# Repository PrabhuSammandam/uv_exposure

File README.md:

# uv_exposure
Source code the uv exposure box.

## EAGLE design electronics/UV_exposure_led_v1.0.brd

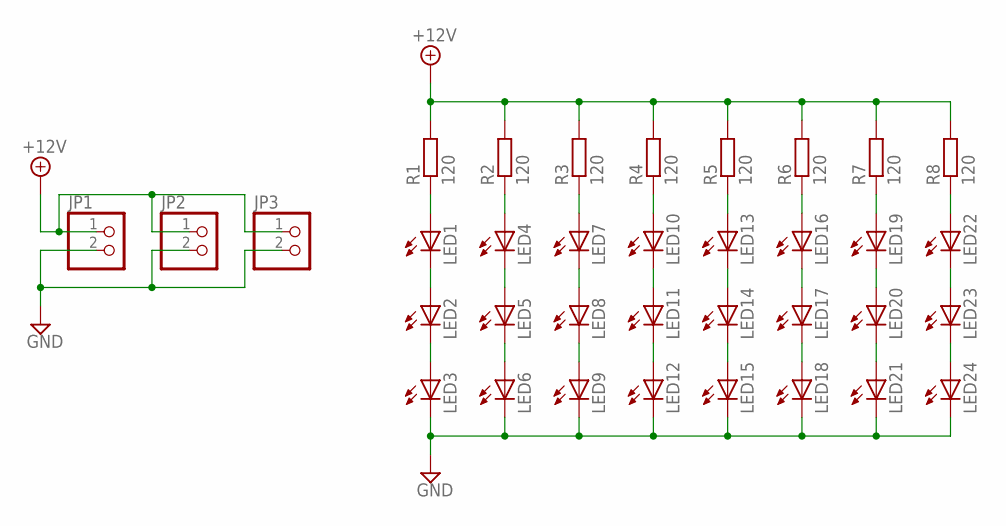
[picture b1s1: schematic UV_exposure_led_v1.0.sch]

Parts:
JP1, JP2, JP3: PINHD-1X2; 1X02
LED1, LED2, LED3, LED4, LED5, LED6, LED7, LED8, LED9, LED10, LED11, LED12, LED13, LED14, LED15, LED16, LED17, LED18, LED19, LED20, LED21, LED22, LED23, LED24: LED5MM
R1, R2, R3, R4, R5, R6, R7, R8: 120; R1206W

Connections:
+12V: JP1.1, JP2.1, JP3.1, R1.2, R2.2, R3.2, R4.2, R5.2, R6.2, R7.2, R8.2
GND: JP1.2, JP2.2, JP3.2, LED3.K (C), LED6.K (C), LED9.K (C), LED12.K (C), LED15.K (C), LED18.K (C), LED21.K (C), LED24.K (C)
unnamed: LED2.K (C), LED3.A
unnamed: LED1.K (C), LED2.A
unnamed: LED1.A, R1.1
unnamed: LED5.K (C), LED6.A
unnamed: LED4.K (C), LED5.A
unnamed: LED4.A, R2.1
unnamed: LED8.K (C), LED9.A
unnamed: LED7.K (C), LED8.A
unnamed: LED7.A, R3.1
unnamed: LED11.K (C), LED12.A
unnamed: LED10.K (C), LED11.A
unnamed: LED10.A, R4.1
unnamed: LED14.K (C), LED15.A
unnamed: LED13.K (C), LED14.A
unnamed: LED13.A, R5.1
unnamed: LED17.K (C), LED18.A
unnamed: LED16.K (C), LED17.A
unnamed: LED16.A, R6.1
unnamed: LED20.K (C), LED21.A
unnamed: LED19.K (C), LED20.A
unnamed: LED19.A, R7.1
unnamed: LED23.K (C), LED24.A
unnamed: LED22.K (C), LED23.A
unnamed: LED22.A, R8.1

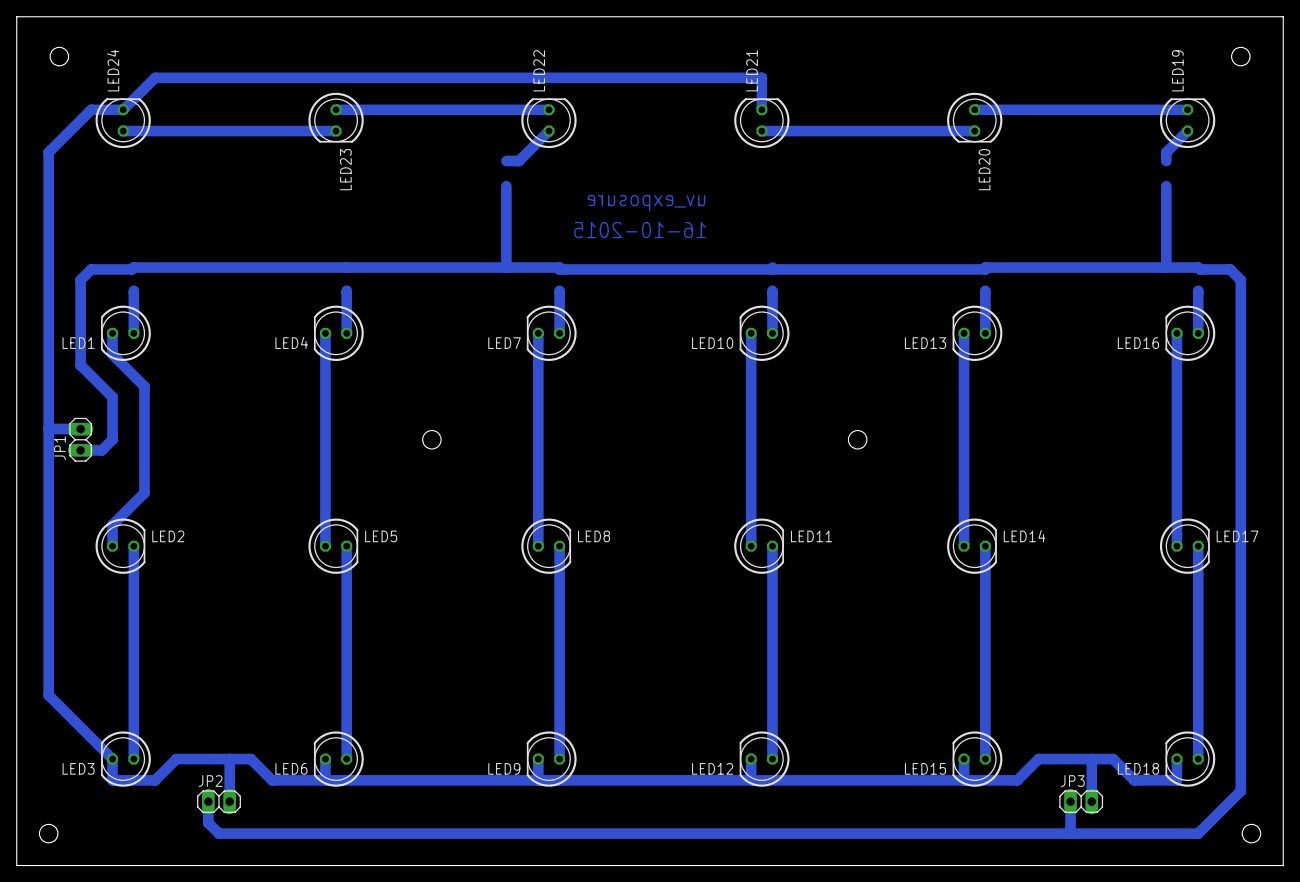
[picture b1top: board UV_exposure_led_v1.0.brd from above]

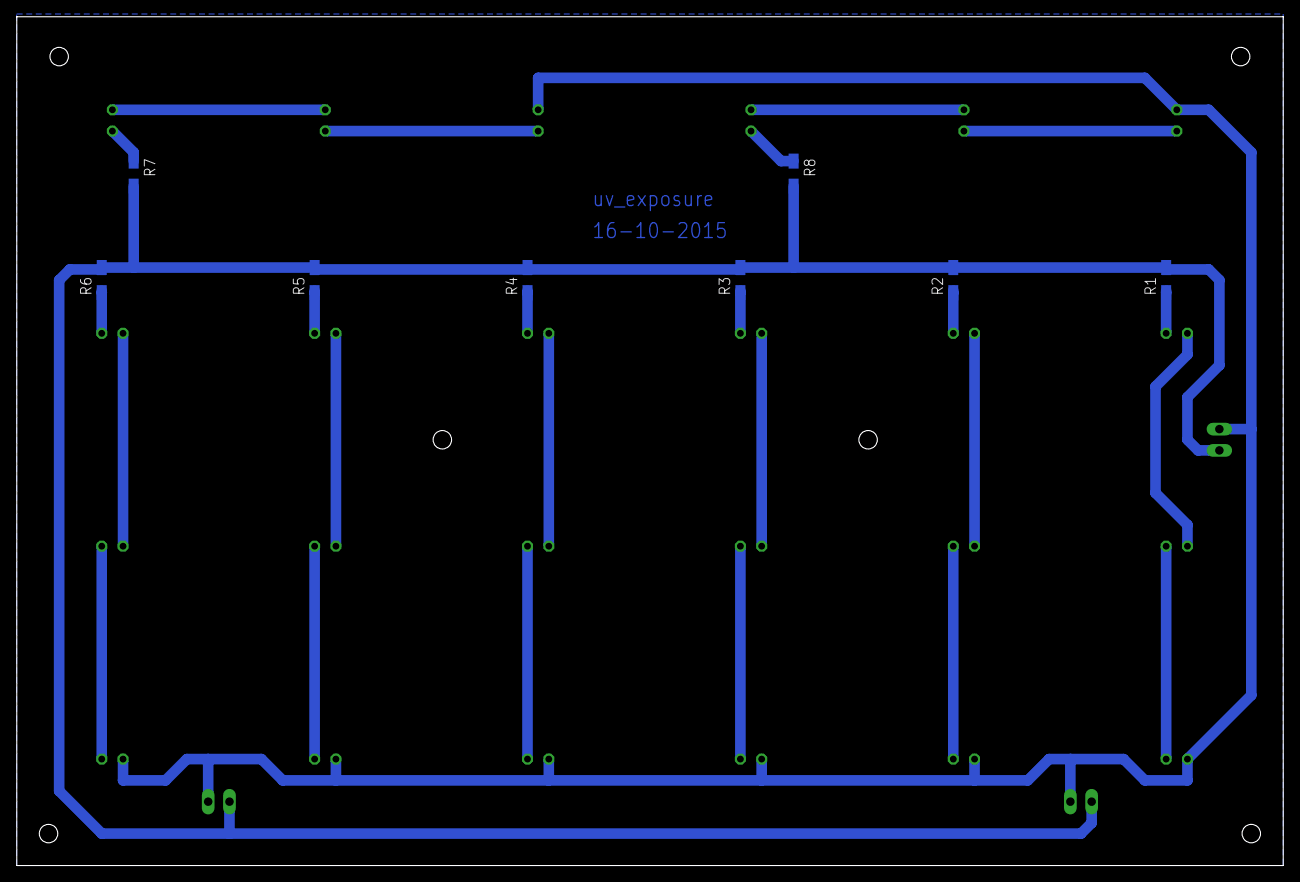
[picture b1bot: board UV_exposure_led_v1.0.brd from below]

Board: 2 copper layers, 151.1 x 101.3 mm, 35 parts (8 on the bottom side), 26 nets.

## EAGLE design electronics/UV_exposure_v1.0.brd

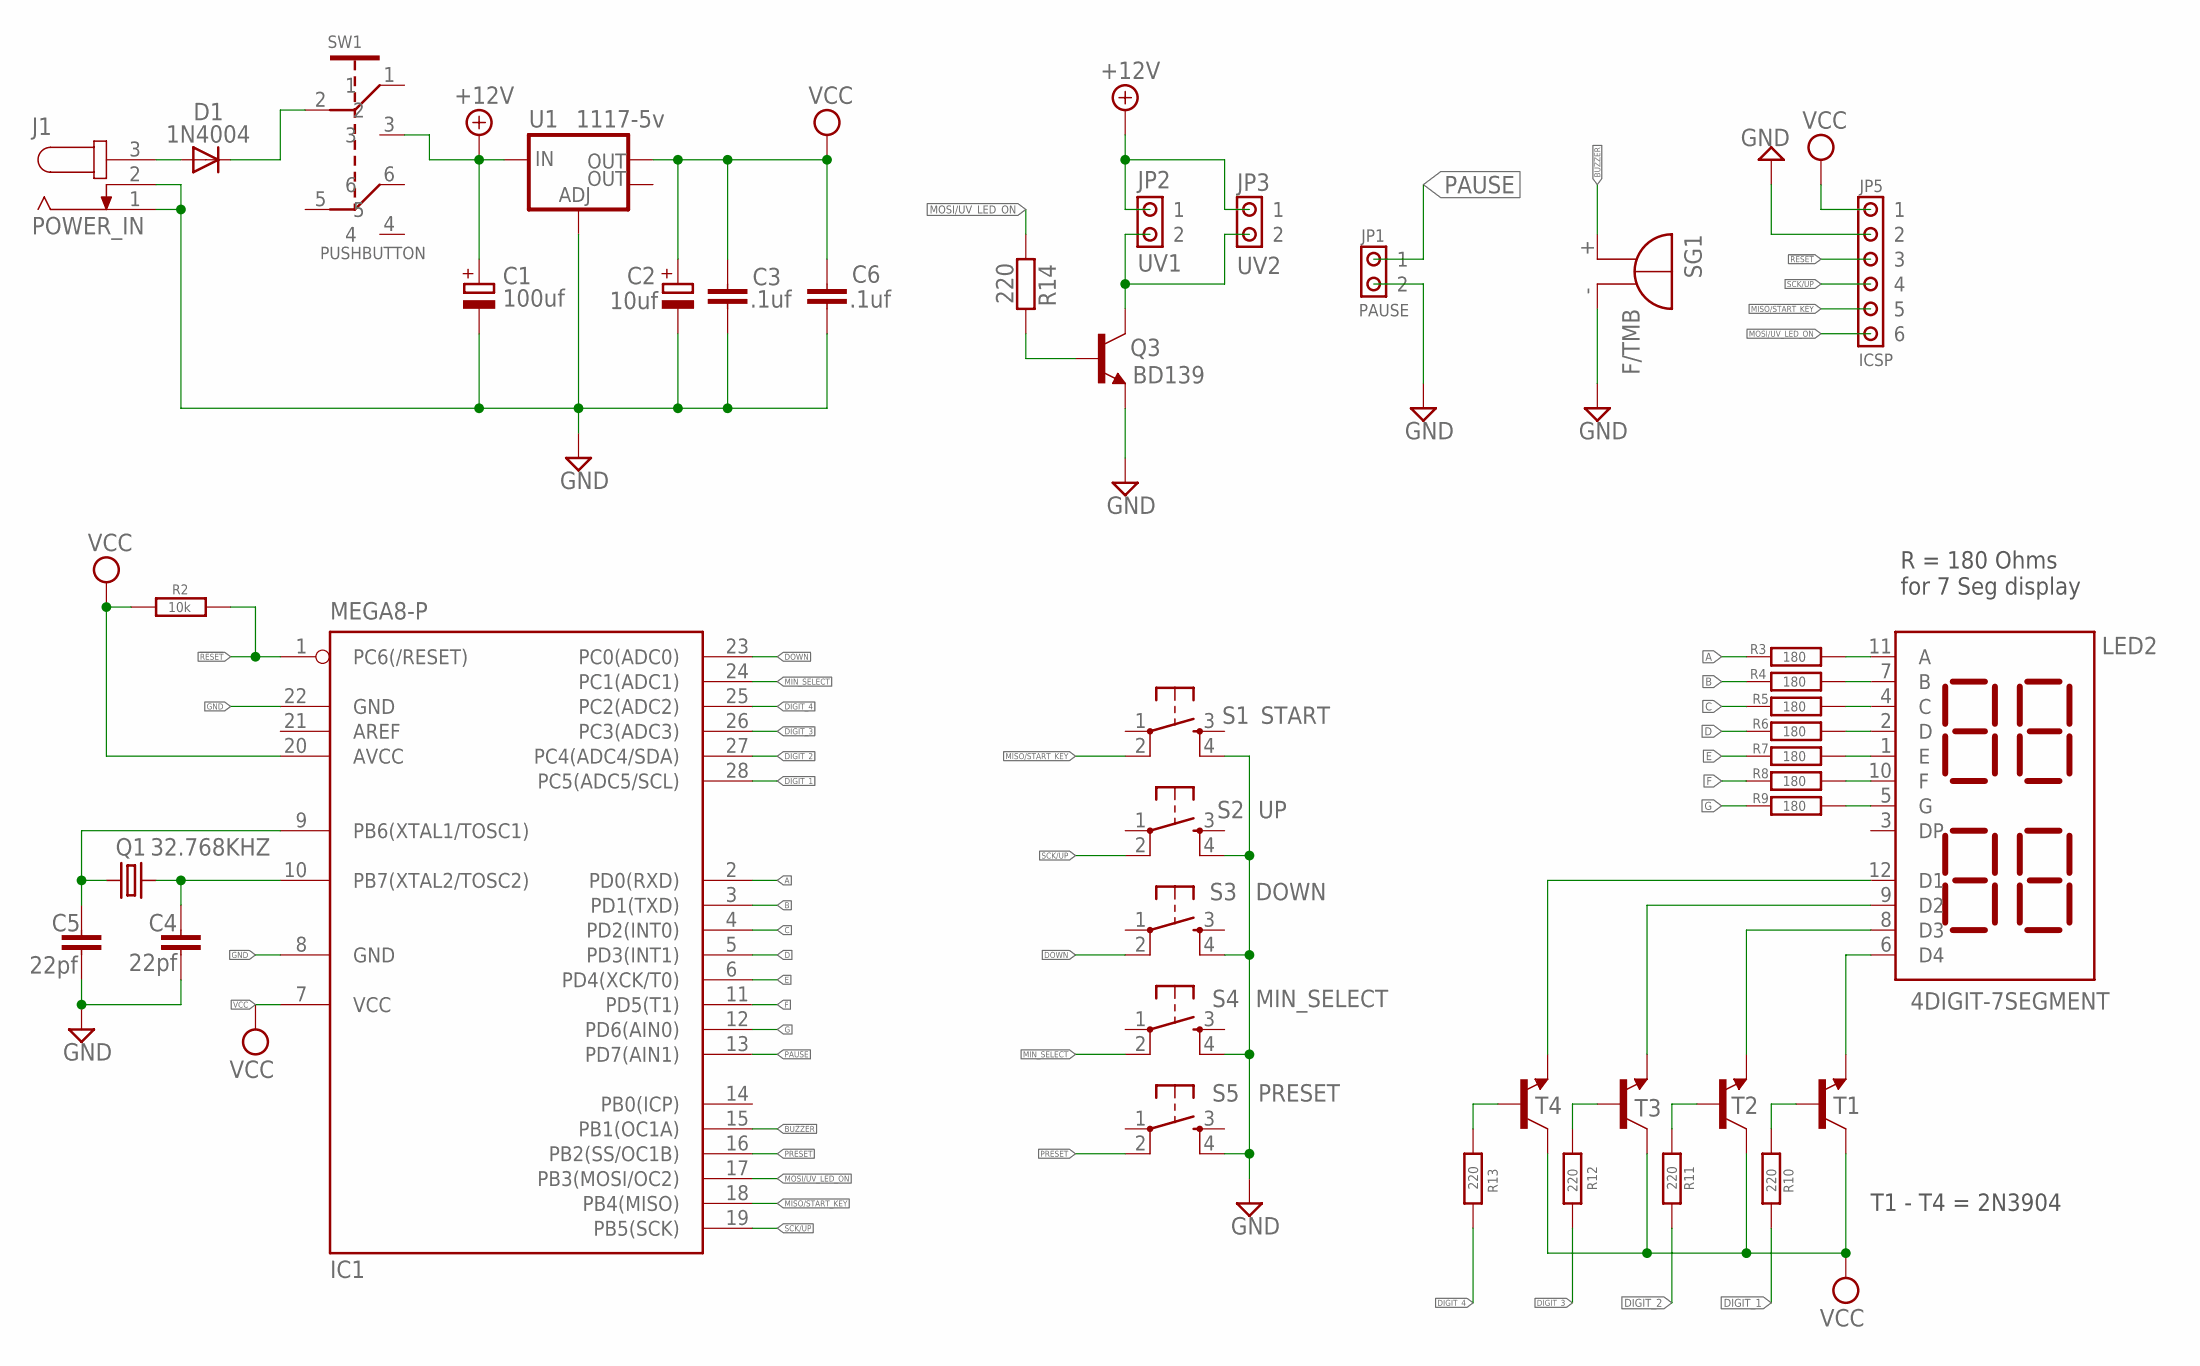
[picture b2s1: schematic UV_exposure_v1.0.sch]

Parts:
C1: 100uf; UD-6,3X7,7_NICHICON
C2: 10uf; 153CLV-0505
C3, C6: .1uf; C0805
C4, C5: 22pf; C0805
D1: 1N4004; DO214AA
IC1: MEGA8-P; DIL28-3
J1: POWER_IN; SPC4078
JP1: PAUSE; 1X2_LONG
JP2: UV1; 1X2_LONG
JP3: UV2; 1X2_LONG
JP5: ICSP; 1X6_LONG
LED2: 4DIGIT-7SEGMENT
Q1: 32.768KHZ; TC26V
Q3: BD139; TO126
R2: 10k; R1206W
R3, R4, R5, R6, R7, R8, R9: 180; R1206W
R10, R11, R12, R13, R14: 220; R1206W
S1: START; B3F-10XX
S2: UP; B3F-10XX
S3: DOWN; B3F-10XX
S4: MIN_SELECT; B3F-10XX
S5: PRESET; B3F-10XX
SG1: F/TMB
SW1: PUSHBUTTON; SPDT-6PIN
T1, T2, T3, T4: 2N3904; SOT23-BEC
U1: 1117-5v; SOT223

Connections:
!RESET: IC1.1 (PC6(/RESET)), JP5.3, R2.1
+12V: C1.+, JP2.1, JP3.1, SW1.3, U1.3 (IN)
A: IC1.2 (PD0(RXD)), R3.2
B: IC1.3 (PD1(TXD)), R4.2
BUZZER: IC1.15 (PB1(OC1A)), SG1.+
C: IC1.4 (PD2(INT0)), R5.2
D: IC1.5 (PD3(INT1)), R6.2
DIGIT_1: IC1.28 (PC5(ADC5/SCL)), R10.2
DIGIT_2: IC1.27 (PC4(ADC4/SDA)), R11.2
DIGIT_3: IC1.26 (PC3(ADC3)), R12.2
DIGIT_4: IC1.25 (PC2(ADC2)), R13.2
DOWN: IC1.23 (PC0(ADC0)), S3.2 (P1)
E: IC1.6 (PD4(XCK/T0)), R7.2
F: IC1.11 (PD5(T1)), R8.2
G: IC1.12 (PD6(AIN0)), R9.2
GND: C1.-, C2.-, C3.2, C4.2, C5.2, C6.2, IC1.8 (GND), IC1.22 (GND), J1.1, J1.2, JP1.2, JP5.2, Q3.1 (E), S1.4 (S1), S2.4 (S1), S3.4 (S1), S4.4 (S1), S5.4 (S1), SG1.-, U1.1 (ADJ)
MIN_SELECT: IC1.24 (PC1(ADC1)), S4.2 (P1)
MISO/START_KEY: IC1.18 (PB4(MISO)), JP5.5, S1.2 (P1)
MOSI/UV_LED_ON: IC1.17 (PB3(MOSI/OC2)), JP5.6, R14.2
unnamed: D1.A, J1.3
unnamed: C4.1, IC1.10 (PB7(XTAL2/TOSC2)), Q1.1
unnamed: D1.C, SW1.2
unnamed: C5.1, IC1.9 (PB6(XTAL1/TOSC1)), Q1.2
unnamed: LED2.11 (A), R3.1
unnamed: LED2.7 (B), R4.1
unnamed: LED2.4 (C), R5.1
unnamed: LED2.2 (D), R6.1
unnamed: LED2.1 (E), R7.1
unnamed: LED2.10 (F), R8.1
unnamed: LED2.5 (G), R9.1
unnamed: LED2.6 (D4), T1.E
unnamed: R10.1, T1.B
unnamed: LED2.8 (D3), T2.E
unnamed: LED2.9 (D2), T3.E
unnamed: LED2.12 (D1), T4.E
unnamed: R13.1, T4.B
unnamed: R12.1, T3.B
unnamed: R11.1, T2.B
unnamed: Q3.3 (B), R14.1
unnamed: JP2.2, JP3.2, Q3.2 (C)
PAUSE: IC1.13 (PD7(AIN1)), JP1.1
PRESET: IC1.16 (PB2(SS/OC1B)), S5.2 (P1)
SCK/UP: IC1.19 (PB5(SCK)), JP5.4, S2.2 (P1)
VCC: C2.+, C3.1, C6.1, IC1.7 (VCC), IC1.20 (AVCC), JP5.1, R2.2, T1.C, T2.C, T3.C, T4.C, U1.2 (OUT)

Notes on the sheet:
R = 180 Ohms for 7 Seg display
T1 - T4 = 2N3904

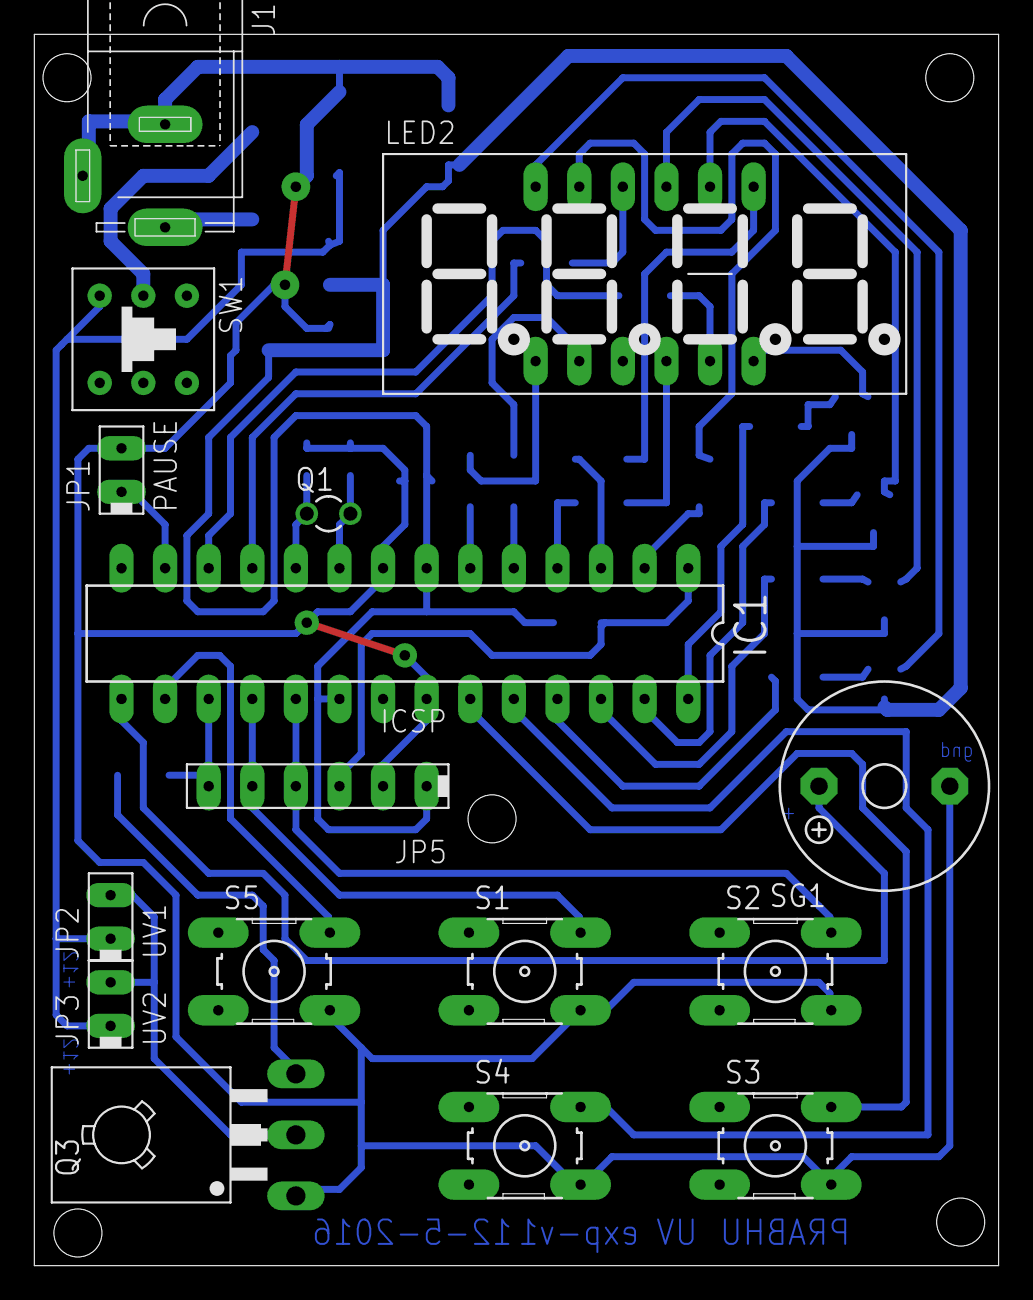
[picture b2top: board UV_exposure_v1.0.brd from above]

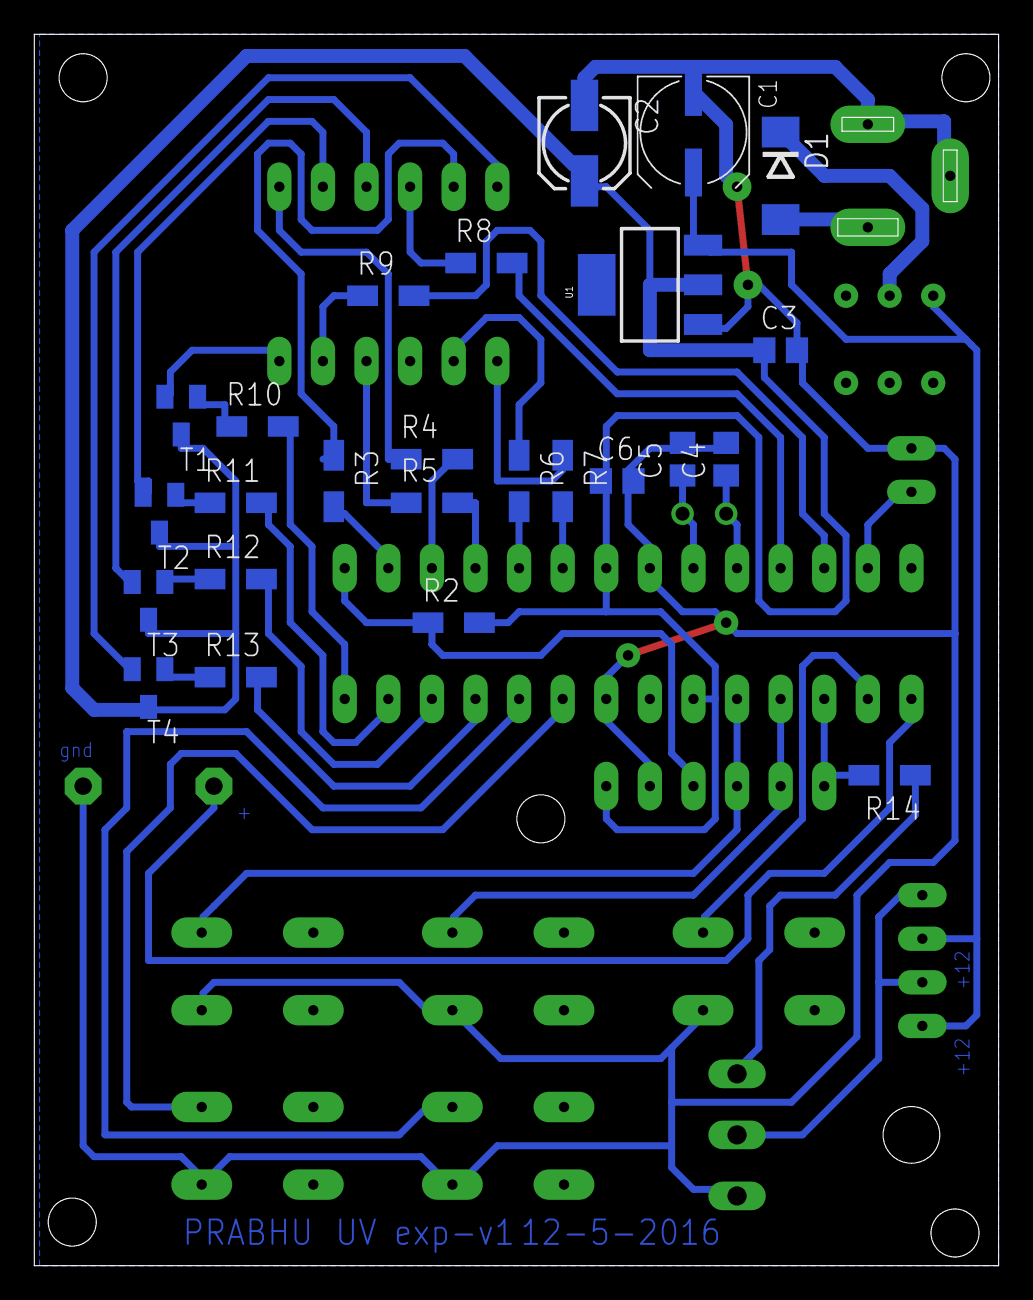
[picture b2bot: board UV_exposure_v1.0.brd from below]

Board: 2 copper layers, 56.2 x 71.7 mm, 41 parts (25 on the bottom side), 44 nets.

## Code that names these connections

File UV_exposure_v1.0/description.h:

/*
 * description.h
 *
 * Created: 10/11/2015 12:49:42 PM
 *  Author: Prabhus
 */ 


#ifndef DESCRIPTION_H_
#define DESCRIPTION_H_

/*
 * 1        -   RESET
 * 2 PD0    -   SEGMENT A
 * 3 PD1    -   SEGMENT B
 * 4 PD2    -   SEGMENT C
 * 5 PD3    -   SEDMENT D
 * 6 PD4    -   SEGMENT E
 * 7        -   VCC
 * 8        -   GND
 * 9        -   XTAL1
 * 10       -   XTAL2
 * 11 PD5   -   SEGMENT F
 * 12 PD6   -   SEGMENT G
 * 13 PD7   -   PAUSE
 * 14       -
 * 15 PB1   -   BUZZER
 * 16 PB2   -   KEY PRESET
 * 17 PB3   -   UV LED
 * 18 PB4   -   KEY START
 * 19 PB5   -   KEY UP
 * 20       -   AVCC
 * 21       -
 * 22       -   GND
 * 23 PC0   -   KEY DOWN
 * 24 PC1   -   KEY MIN_SELECT
 * 25 PC2   -   DIGIT_4
 * 26 PC3   -   DIGIT_3
 * 27 PC4   -   DIGIT_2
 * 28 PC5   -   DIGIT_1
 *
 * uC           =   ATMEGA8L
 * Clock        =   Internal 8Mhz RC oscillator
 * Low Fuse     =   0xE4
 * High Fuse    =   0xc9
 *
1.	 Internal 8MHZ oscillator.
2.	 Timer2 for RTC.
3.	 Timer0 for display refresh.

Timer0:
	 Clock Source	 :	  Internal 8MHZ
	 Prescale			 :	  64

	 Timer0 input => 8000000/64 => 125000 Hz => 0.000008 => 8 uS
	 Timer0 interrupt => 256 * 8uS => 2.048 mS

	 Each digit got refreshed by 2.048 mS.

Timer2:
	 Clock Source	 :	  32.768kHz 
	 Prescale		 :	  128

	 Timer2 input => 32768/128 => 256 => 0.00390625

	 Timer2 interrupt => 256 * 0.00390625 => 1 Sec

*/



#endif /* DESCRIPTION_H_ */

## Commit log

2016-06-04 Atmel studio updated
2016-06-04 Added .gitignore file
2016-06-04 Added the schematic and board file.
2016-06-06 changed the SetStandby signature. Minor improvements.

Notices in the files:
parts and their libraries:
SparkFun-PowerIC: Licensing: Creative Commons ShareAlike 4.0 International - https://creativecommons.org/licenses/by-sa/4.0
